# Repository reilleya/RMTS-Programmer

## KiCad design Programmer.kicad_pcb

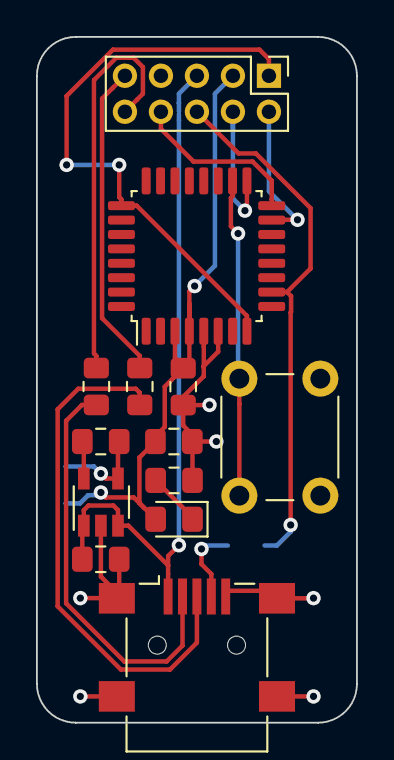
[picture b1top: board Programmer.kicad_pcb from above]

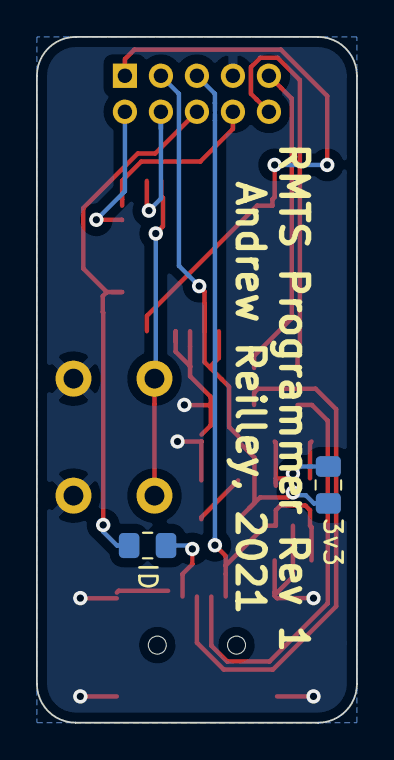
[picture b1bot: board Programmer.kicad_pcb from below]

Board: 2 copper layers, 17.8 x 38.1 mm, 15 parts (2 on the bottom side), 17 nets.

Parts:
3v3: 0; R_0805_2012Metric_Pad1.15x1.40mm_HandSolder
C1: 10uF; C_0805_2012Metric_Pad1.15x1.40mm_HandSolder
C2: 0.1uF; C_0805_2012Metric_Pad1.15x1.40mm_HandSolder
C3: 4.7uF; C_0805_2012Metric_Pad1.15x1.40mm_HandSolder
D1: LED; LED_0805_2012Metric_Pad1.15x1.40mm_HandSolder
ID: 0; R_0805_2012Metric_Pad1.15x1.40mm_HandSolder
J1: USB_B_Micro; USB_Mini-B_Lumberg_2486_01_Horizontal
J2: Conn_02x05_Odd_Even; PinHeader_2x05_P2.00mm_Vertical
L1: 1uH; L_0805_2012Metric_Pad1.15x1.40mm_HandSolder
R1, R2: 33; R_0805_2012Metric_Pad1.15x1.40mm_HandSolder
R3: 500; R_0805_2012Metric_Pad1.15x1.40mm_HandSolder
SW1: SW_Push; SW_PUSH_6mm
U1: MKL04Z32VLC4; LQFP-32_7x7mm_P0.8mm
U2: ADP2108AUJ-3.3; TSOT-23-5

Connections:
+3V3: 3v3.1, C1.1, C2.1, D1.2, J2.3, U1.3, U1.4
+5V: C3.1, J1.1, J2.5, U2.1, U2.3
/PTA0: J2.8, U1.16
/PTA1: ID.1, J2.6, U1.10
/PTA2: J2.4, U1.17
/PTA3: J2.2, U1.15
/RST: J2.1, U1.8, U1.25
/USBM: J2.10, R2.2
/USBP: J2.9, R1.2
GND: C1.2, C2.2, C3.2, J1.5, J1.6, J2.7, R3.2, SW1.1, U1.5, U1.6, U2.2
unnamed: D1.1, R3.1
unnamed: J1.2, R2.1
unnamed: J1.3, R1.1
unnamed: ID.2, J1.4
unnamed: L1.1, U2.5
unnamed: 3v3.2, L1.2, U2.4
unnamed: SW1.2, U1.18

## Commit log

2021-01-16 Initial commit with basic schematic and layout
2021-01-17 Rounded corners, added LED
2021-01-23 Added silkscreen
2021-01-30 Add input cap
2021-01-30 Provide 5v to target
2021-02-07 Add 0 ohm resistor to ID pin, cleanup
2021-02-08 Annotate
2021-02-22 Rev 1
